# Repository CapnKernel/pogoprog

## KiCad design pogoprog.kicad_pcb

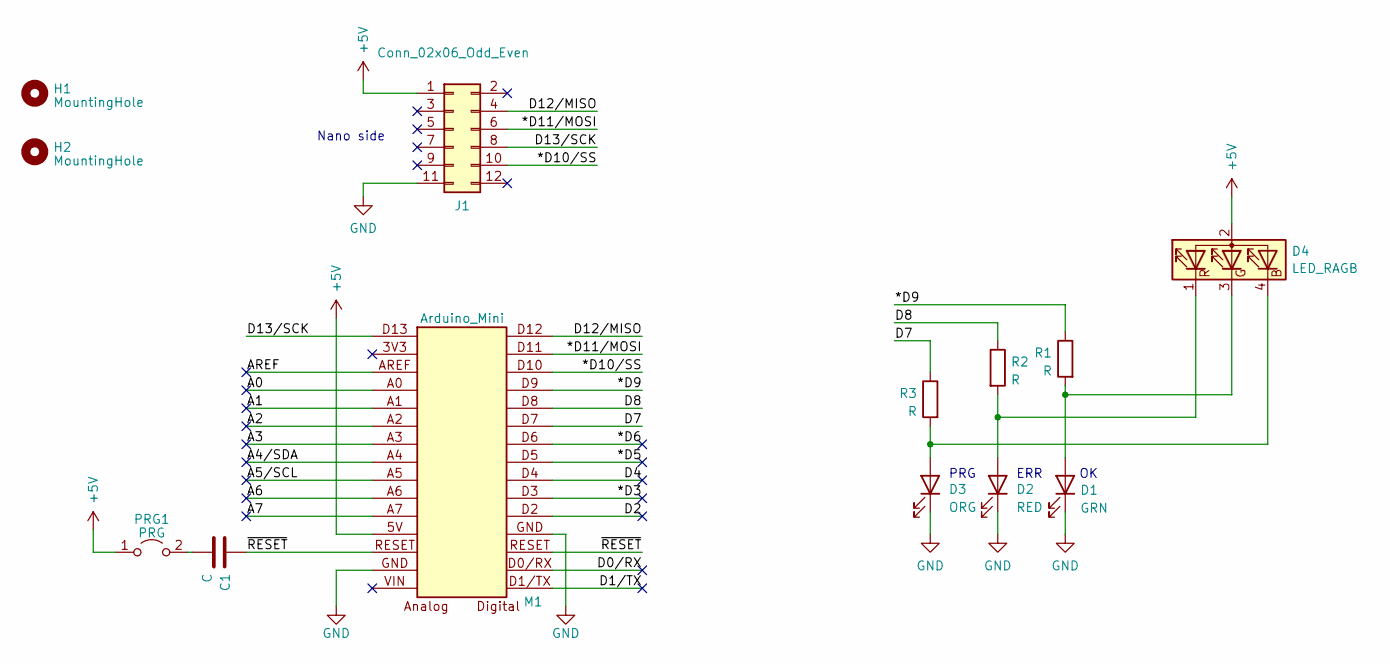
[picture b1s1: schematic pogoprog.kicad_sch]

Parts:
C1: C; C_0805_2012Metric_Pad1.18x1.45mm_HandSolder
D1: GRN; LED_0805_2012Metric_Pad1.15x1.40mm_HandSolder
D2: RED; LED_0805_2012Metric_Pad1.15x1.40mm_HandSolder
D3: ORG; LED_0805_2012Metric_Pad1.15x1.40mm_HandSolder
D4: LED_RAGB; LED_D8.0mm-4_RGB
H1, H2: MountingHole; MountingHole_2.2mm_M2
J1: Conn_02x06_Odd_Even; PinHeader_2x06_P2.54mm_Vertical
M1: Arduino_Mini; Arduino Mini
PRG1: PRG; SolderJumper-2_P1.3mm_Open_Pad1.0x1.5mm
R1, R2, R3: R; R_0805_2012Metric_Pad1.20x1.40mm_HandSolder

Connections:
+5V: D4.2 (A), J1.1, M1.5V, PRG1.1 (A)
/*D3: M1.D3
/*D5: M1.D5
/*D6: M1.D6
/*D9: M1.D9, R1.1
/*D10/SS: J1.10, M1.D10
/*D11/MOSI: J1.6, M1.D11
/A0: M1.A0
/A1: M1.A1
/A2: M1.A2
/A3: M1.A3
/A4/SDA: M1.A4
/A5/SCL: M1.A5
/A6: M1.A6
/A7: M1.A7
/AREF: M1.AREF
/D0/RX: M1.D0/RX
/D1/TX: M1.D1/TX
/D2: M1.D2
/D4: M1.D4
/D7: M1.D7, R3.1
/D8: M1.D8, R2.1
/D12/MISO: J1.4, M1.D12
/D13/SCK: J1.8, M1.D13
/~RESET: C1.1, M1.RESET
GND: D1.1 (K), D2.1 (K), D3.1 (K), J1.11, M1.GND
unnamed: D1.2 (A), D4.3 (GK), R1.2
unnamed: D2.2 (A), D4.1 (RK), R2.2
unnamed: D3.2 (A), D4.4 (BK), R3.2
unnamed: C1.2, PRG1.2 (B)

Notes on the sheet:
Nano side
PRG
ERR

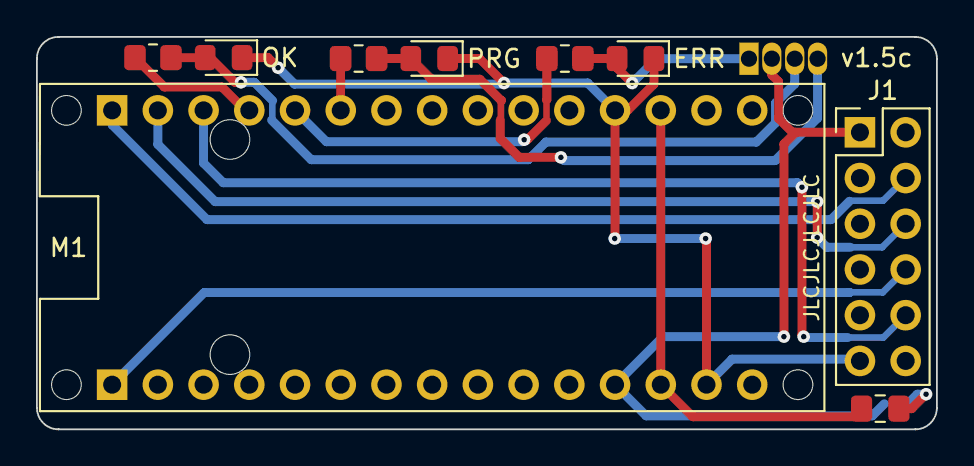
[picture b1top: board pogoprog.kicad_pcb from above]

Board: 2 copper layers, 50.0 x 21.8 mm, 13 parts (1 on the bottom side), 14 nets.

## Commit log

2023-05-10 Third version, reduced size to fit within 50mm.
    Previous versions are not in git.
2023-05-31 Converted back to 2 layer, as I got the connector size wrong.
    Should be 2x6 x 2.54mm pitch
2023-05-31 Moved version number to be on-board.
2023-08-14 Moved some silkscreen text.
2023-08-14 Added pads for a common-anode 8mm RGB LED
2023-09-15 Fixed a bent silkscreen line
2023-09-15 Last minute tweaks
    Improved silkscreen for LED labels.
    Added text to back showing connector pinout
    Moved M1
    Renamed J3 to J1
